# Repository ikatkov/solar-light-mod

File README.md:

# Solar light reverse eng and mods

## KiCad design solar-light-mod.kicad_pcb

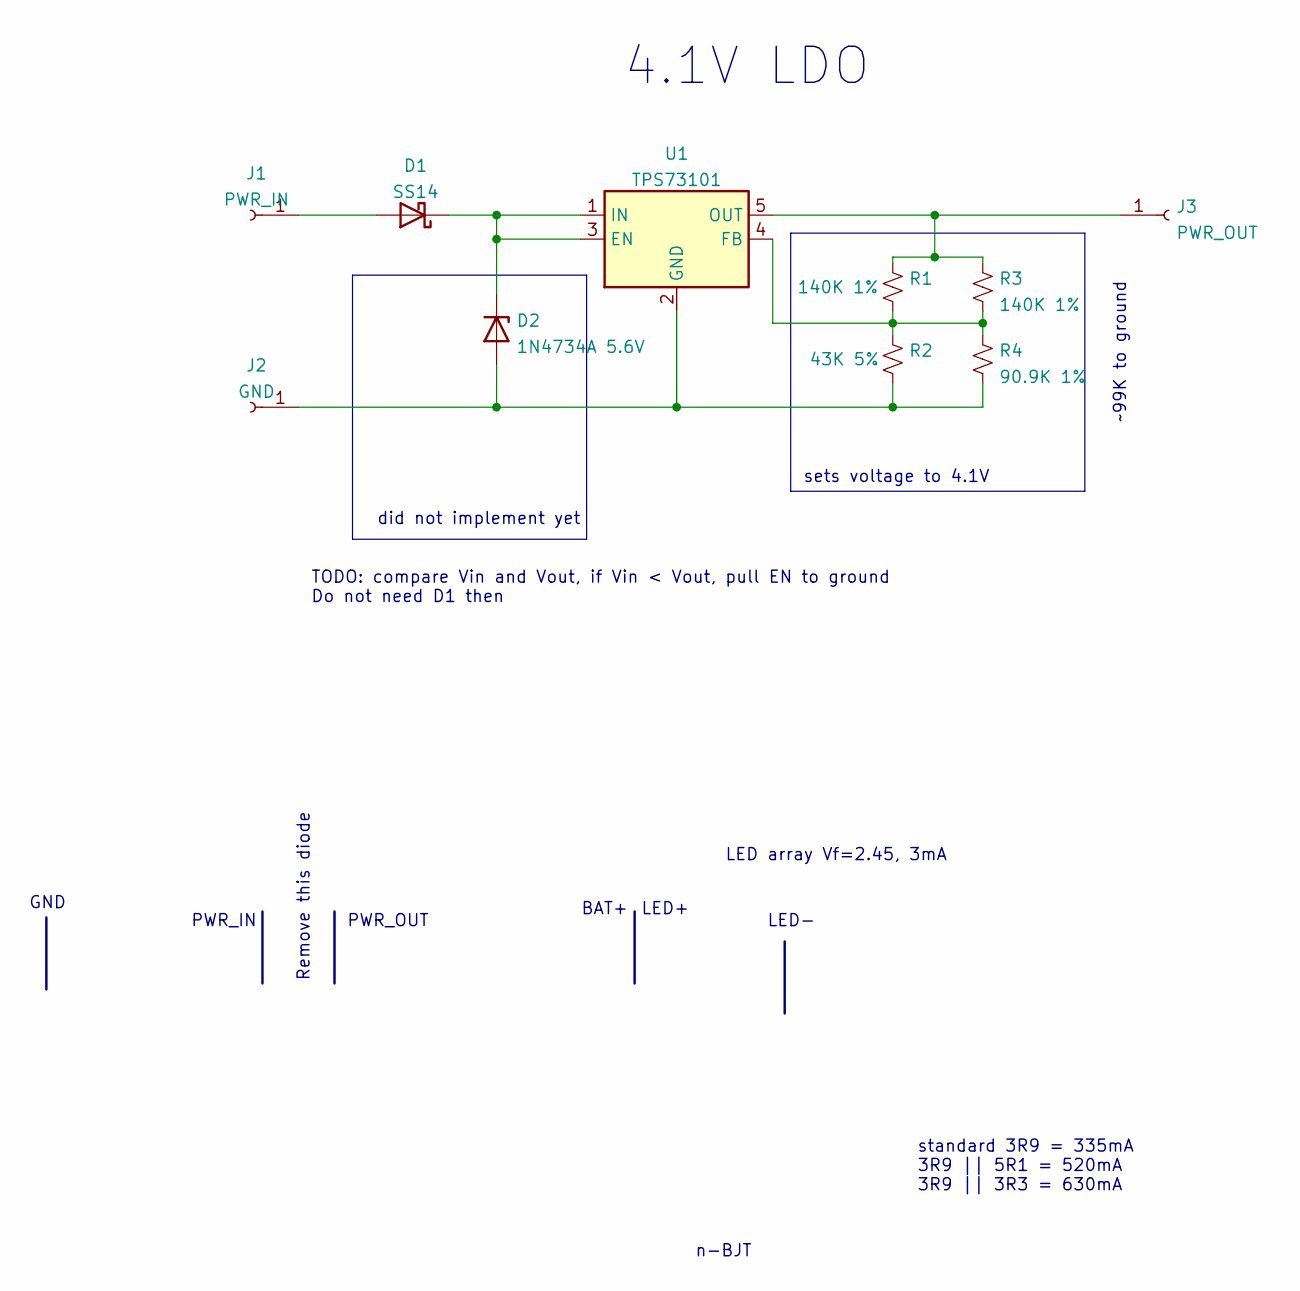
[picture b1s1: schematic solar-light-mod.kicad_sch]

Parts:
D1: SS14; D_SMA_Handsoldering
D2: 1N4734A 5.6V
J1: PWR_IN; PinHeader_1x01_P2.54mm_Vertical
J2: GND; PinHeader_1x01_P2.54mm_Vertical
J3: PWR_OUT; PinHeader_1x01_P2.54mm_Vertical
R1, R3: 140K 1%; R_0805_2012Metric_Pad1.20x1.40mm_HandSolder
R2: 43K 5%; R_0805_2012Metric_Pad1.20x1.40mm_HandSolder
R4: 90.9K 1%; R_0805_2012Metric_Pad1.20x1.40mm_HandSolder
U1: TPS73101; SOT-23-5

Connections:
unnamed: D1.1 (K), D2.1 (K), U1.1 (IN), U1.3 (EN)
unnamed: D1.2 (A), J1.1
unnamed: D2.2 (A), J2.1, R2.2, R4.2, U1.2 (GND)
unnamed: J3.1, R1.1, R3.1, U1.5 (OUT)
unnamed: R1.2, R2.1, R3.2, R4.1, U1.4 (FB)

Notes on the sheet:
LED array Vf=2.45, 3mA
LED+
4.1V LDO
GND
PWR_IN
did not implement yet
standard 3R9 = 335mA 3R9 || 5R1 = 520mA 3R9 || 3R3 = 630mA
n-BJT
Remove this diode
TODO: compare Vin and Vout, if Vin < Vout, pull EN to ground Do not need D1 then
PWR_OUT
LED-
sets voltage to 4.1V
BAT+
~99K to ground

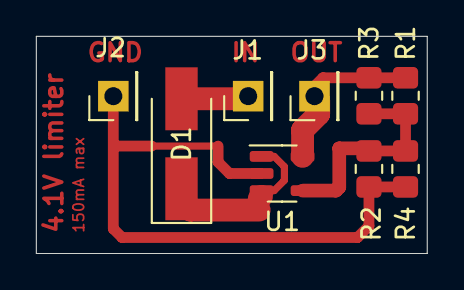
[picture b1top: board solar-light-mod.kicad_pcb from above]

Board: 4 copper layers, 21.7 x 12.1 mm, 9 parts (0 on the bottom side), 5 nets.

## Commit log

2022-11-18 Initial
